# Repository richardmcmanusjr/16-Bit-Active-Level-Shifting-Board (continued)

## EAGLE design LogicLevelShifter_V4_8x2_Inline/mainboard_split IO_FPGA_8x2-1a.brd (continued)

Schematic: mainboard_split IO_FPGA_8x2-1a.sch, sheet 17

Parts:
C94, C95: 0.1uF; C0805
C96, C97: 2.2uF; C0805
FROM_FPGA_20: PINHD-1X1; 1X01
JP_DRAIN19: PINHD-1X1; 1X01
JP_GATE20: PINHD-1X1; 1X01
JP_MIPS20: PINHD-1X1; 1X01
R186, R190, R192: 130; R0805
R187: 130; R0603
R188, R189, R191, R193, R194: 220; R0805
S39, S40: SM-3TW102; SM3TW102
TO_FPGA_20: PINHD-1X1; 1X01
U44, U45: TLV3501AID; D8

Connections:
+1.5V: C94.2, C96.2, S39.1 (CCW), S40.1 (CCW), U44.7 (V+); also elsewhere on the board
+3V: C95.1, C97.1, U45.7 (V+); also elsewhere on the board
-1.5V: C94.1, C96.1, S39.3 (CW), U44.4 (V-); also elsewhere on the board
DIR_GATE: JP_GATE20.1, R194.2; also elsewhere on the board
F16: FROM_FPGA_20.1, R187.1; also elsewhere on the board
GND: C95.2, C97.2, R189.2, R193.2, S40.3 (CW), U45.4 (V-); also elsewhere on the board
INV_DIR_DRAIN: JP_DRAIN19.1, U45.8 (SHDN); also elsewhere on the board
M16: JP_MIPS20.1, R191.2, R192.1, R193.1; also elsewhere on the board
unnamed: R186.2, S39.2 (WIPER)
unnamed: R186.1, U44.2 (IN-)
unnamed: R188.1, U45.6 (OUT)
unnamed: R190.1, S40.2 (WIPER)
unnamed: R190.2, U45.2 (IN-)
unnamed: R192.2, U45.3 (IN+)
unnamed: R191.1, U44.6 (OUT)
unnamed: R194.1, U44.8 (SHDN)
unnamed: R187.2, U44.3 (IN+)
TF16: R188.2, R189.1, TO_FPGA_20.1; also elsewhere on the board

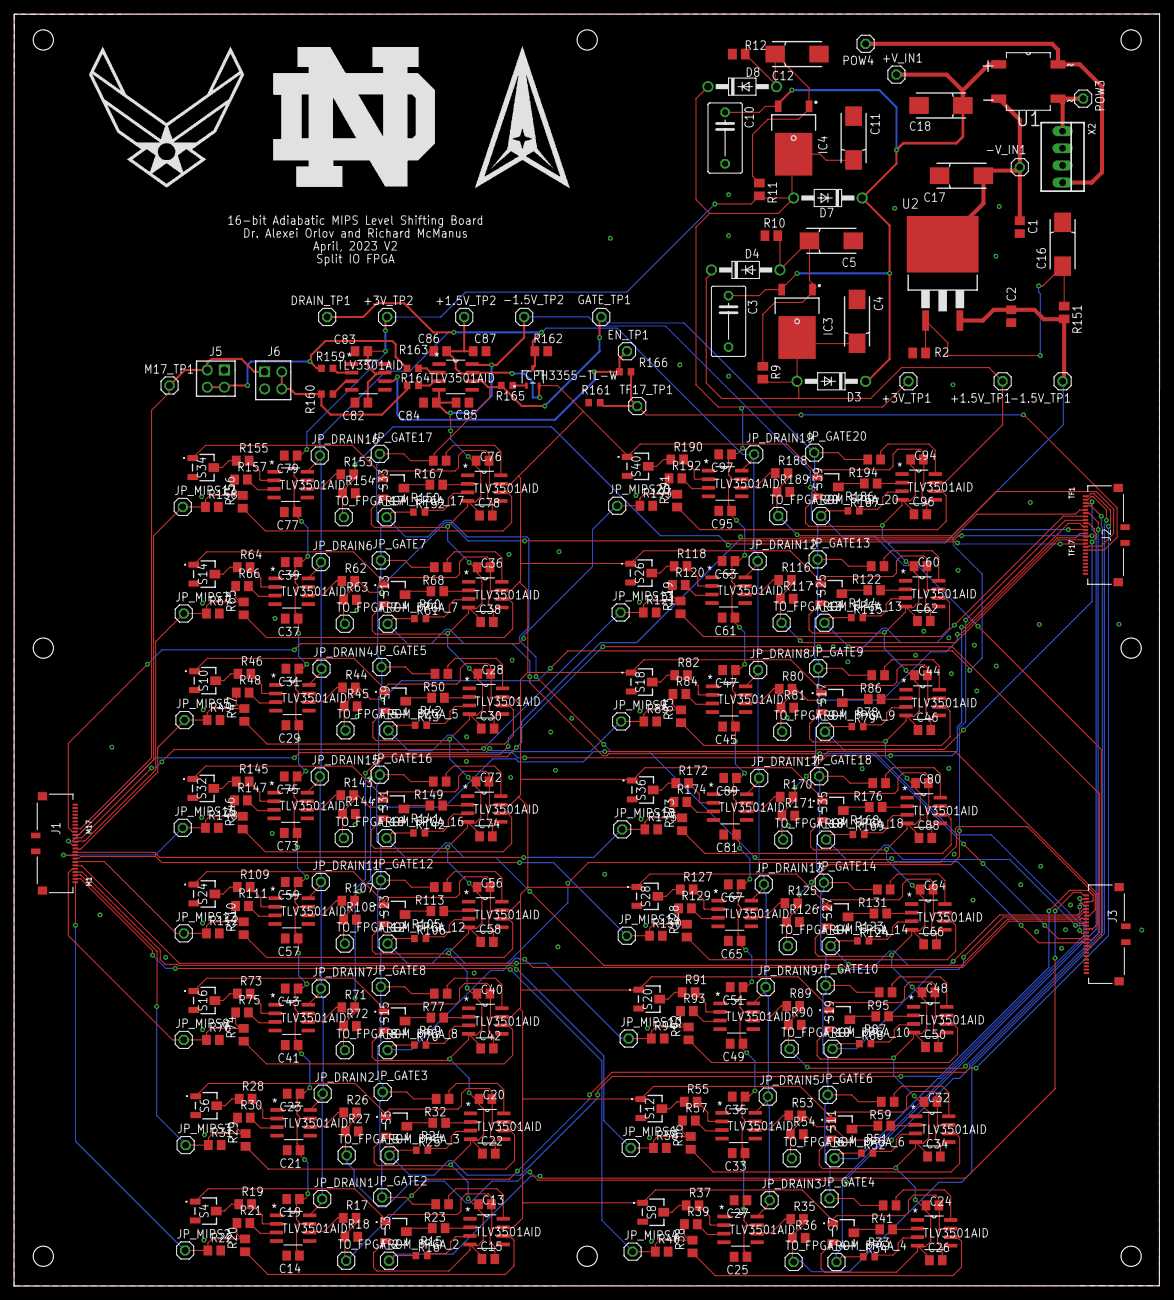
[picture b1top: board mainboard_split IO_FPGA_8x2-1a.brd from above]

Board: 2 copper layers, 169.8 x 188.6 mm, 415 parts (0 on the bottom side), 215 nets.

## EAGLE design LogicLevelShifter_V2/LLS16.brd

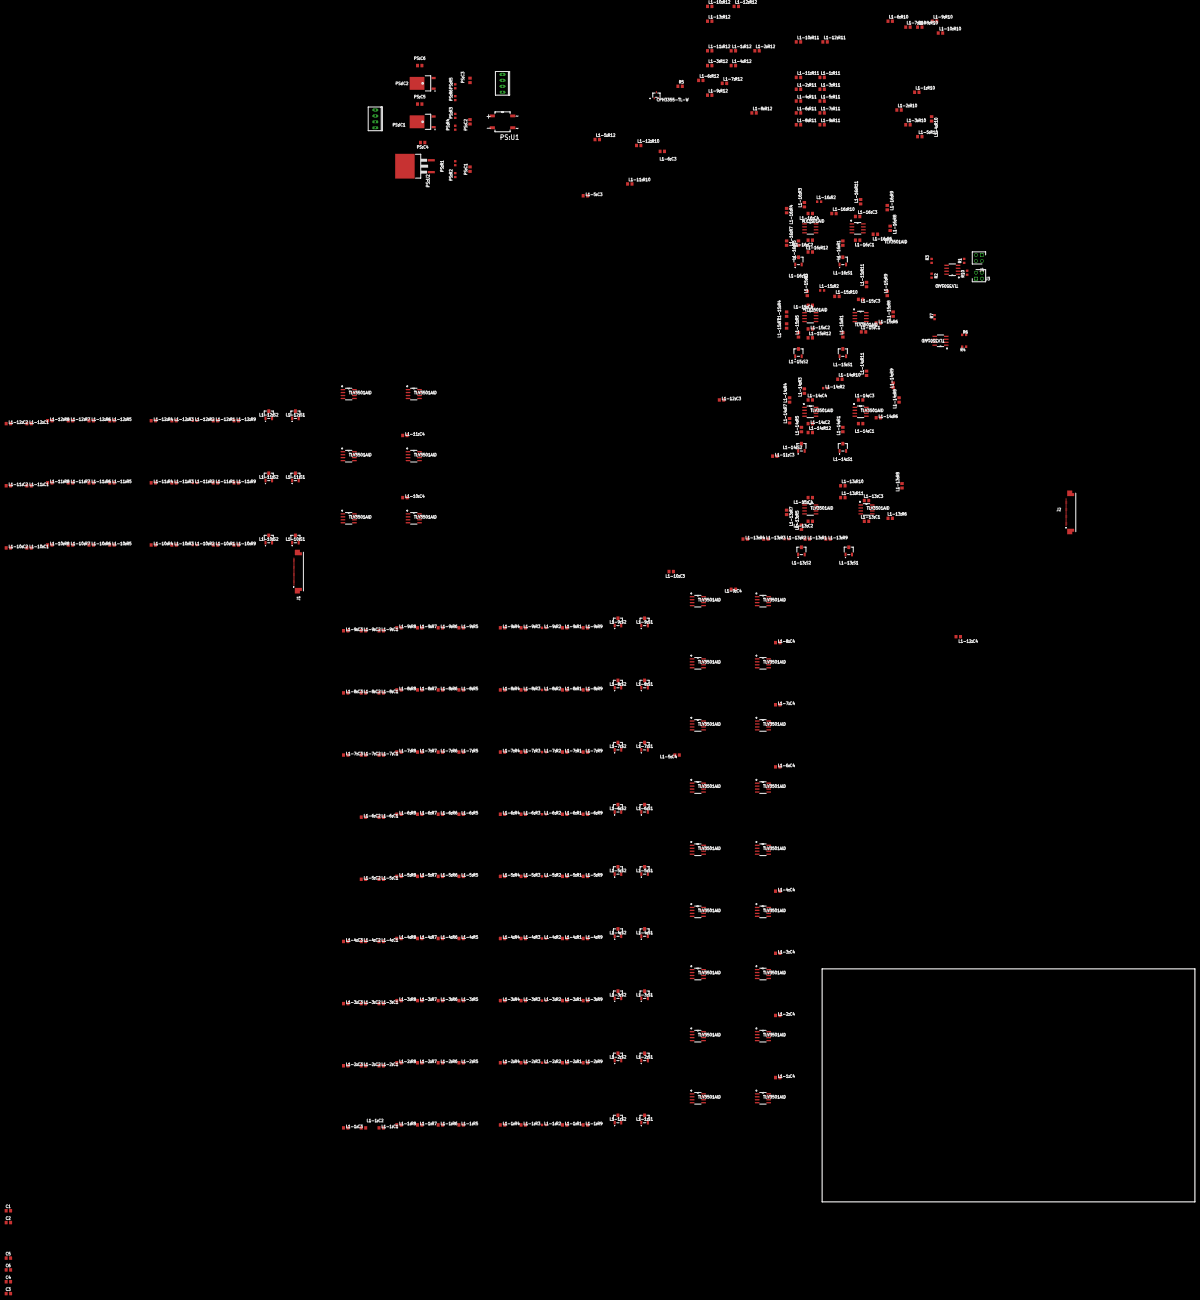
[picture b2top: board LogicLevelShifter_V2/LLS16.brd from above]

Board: 2 copper layers, 160.0 x 100.0 mm, 359 parts (0 on the bottom side), 264 nets, no tracks yet.

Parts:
C1, C2, C3, C4, C5, C6: C0805
J1, J2: 0524372471
J3, J4: 70287-1098; HDRV4W64P254_2X2_521X508X851P
L1-1:C1, L1-1:C2, L1-1:C3, L1-1:C4, L1-2:C1, L1-2:C2, L1-2:C3, L1-2:C4, L1-3:C1, L1-3:C2, L1-3:C3, L1-3:C4, L1-4:C1, L1-4:C2, L1-4:C3, L1-4:C4, L1-5:C1, L1-5:C2, L1-5:C3, L1-5:C4, L1-6:C1, L1-6:C2, L1-6:C3, L1-6:C4, L1-7:C1, L1-7:C2, L1-7:C3, L1-7:C4, L1-8:C1, L1-8:C2, L1-8:C3, L1-8:C4, L1-9:C1, L1-9:C2, L1-9:C3, L1-9:C4, L1-10:C1, L1-10:C2, L1-10:C3, L1-10:C4, L1-11:C1, L1-11:C2, L1-11:C3, L1-11:C4, L1-12:C1, L1-12:C2, L1-12:C3, L1-12:C4, L1-13:C1, L1-13:C2, L1-13:C3, L1-13:C4, L1-14:C1, L1-14:C2, L1-14:C3, L1-14:C4, L1-15:C1, L1-15:C2, L1-15:C3, L1-15:C4, L1-16:C1, L1-16:C2, L1-16:C3, L1-16:C4: C0805
L1-1:R1, L1-1:R5, L1-1:R7, L1-2:R1, L1-2:R5, L1-2:R7, L1-3:R1, L1-3:R5, L1-3:R7, L1-4:R1, L1-4:R5, L1-4:R7, L1-5:R1, L1-5:R5, L1-5:R7, L1-6:R1, L1-6:R5, L1-6:R7, L1-7:R1, L1-7:R5, L1-7:R7, L1-8:R1, L1-8:R5, L1-8:R7, L1-9:R1, L1-9:R5, L1-9:R7, L1-10:R1, L1-10:R5, L1-10:R7, L1-11:R1, L1-11:R5, L1-11:R7, L1-12:R1, L1-12:R5, L1-12:R7, L1-13:R1, L1-13:R5, L1-13:R7, L1-14:R1, L1-14:R5, L1-14:R7, L1-15:R1, L1-15:R5, L1-15:R7, L1-16:R1, L1-16:R5, L1-16:R7: 130; R0805
L1-1:R2, L1-2:R2, L1-3:R2, L1-4:R2, L1-5:R2, L1-6:R2, L1-7:R2, L1-8:R2, L1-9:R2, L1-10:R2, L1-11:R2, L1-12:R2, L1-13:R2, L1-14:R2, L1-15:R2, L1-16:R2: 130; R0603
L1-1:R3, L1-1:R4, L1-1:R6, L1-1:R8, L1-1:R9, L1-2:R3, L1-2:R4, L1-2:R6, L1-2:R8, L1-2:R9, L1-3:R3, L1-3:R4, L1-3:R6, L1-3:R8, L1-3:R9, L1-4:R3, L1-4:R4, L1-4:R6, L1-4:R8, L1-4:R9, L1-5:R3, L1-5:R4, L1-5:R6, L1-5:R8, L1-5:R9, L1-6:R3, L1-6:R4, L1-6:R6, L1-6:R8, L1-6:R9, L1-7:R3, L1-7:R4, L1-7:R6, L1-7:R8, L1-7:R9, L1-8:R3, L1-8:R4, L1-8:R6, L1-8:R8, L1-8:R9, L1-9:R3, L1-9:R4, L1-9:R6, L1-9:R8, L1-9:R9, L1-10:R3, L1-10:R4, L1-10:R6, L1-10:R8, L1-10:R9, L1-11:R3, L1-11:R4, L1-11:R6, L1-11:R8, L1-11:R9, L1-12:R3, L1-12:R4, L1-12:R6, L1-12:R8, L1-12:R9, L1-13:R3, L1-13:R4, L1-13:R6, L1-13:R8, L1-13:R9, L1-14:R3, L1-14:R4, L1-14:R6, L1-14:R8, L1-14:R9, L1-15:R3, L1-15:R4, L1-15:R6, L1-15:R8, L1-15:R9, L1-16:R3, L1-16:R4, L1-16:R6, L1-16:R8, L1-16:R9: 220; R0805
L1-1:R10, L1-1:R11, L1-1:R12, L1-2:R10, L1-2:R11, L1-2:R12, L1-3:R10, L1-3:R11, L1-3:R12, L1-4:R10, L1-4:R11, L1-4:R12, L1-5:R10, L1-5:R11, L1-5:R12, L1-6:R10, L1-6:R11, L1-6:R12, L1-7:R10, L1-7:R11, L1-7:R12, L1-8:R10, L1-8:R11, L1-8:R12, L1-9:R10, L1-9:R11, L1-9:R12, L1-10:R10, L1-10:R11, L1-10:R12, L1-11:R10, L1-11:R11, L1-11:R12, L1-12:R10, L1-12:R11, L1-12:R12, L1-13:R10, L1-13:R11, L1-13:R12, L1-14:R10, L1-14:R11, L1-14:R12, L1-15:R10, L1-15:R11, L1-15:R12, L1-16:R10, L1-16:R11, L1-16:R12: 0; R0805
L1-1:S1, L1-1:S2, L1-2:S1, L1-2:S2, L1-3:S1, L1-3:S2, L1-4:S1, L1-4:S2, L1-5:S1, L1-5:S2, L1-6:S1, L1-6:S2, L1-7:S1, L1-7:S2, L1-8:S1, L1-8:S2, L1-9:S1, L1-9:S2, L1-10:S1, L1-10:S2, L1-11:S1, L1-11:S2, L1-12:S1, L1-12:S2, L1-13:S1, L1-13:S2, L1-14:S1, L1-14:S2, L1-15:S1, L1-15:S2, L1-16:S1, L1-16:S2: SM-3TW102; SM3TW102
L1-1:U1, L1-1:U2, L1-2:U1, L1-2:U2, L1-3:U1, L1-3:U2, L1-4:U1, L1-4:U2, L1-5:U1, L1-5:U2, L1-6:U1, L1-6:U2, L1-7:U1, L1-7:U2, L1-8:U1, L1-8:U2, L1-9:U1, L1-9:U2, L1-10:U1, L1-10:U2, L1-11:U1, L1-11:U2, L1-12:U1, L1-12:U2, L1-13:U1, L1-13:U2, L1-14:U1, L1-14:U2, L1-15:U1, L1-15:U2, L1-16:U1, L1-16:U2: TLV3501AID; D8
PS:C1, PS:C2, PS:C3: 10uF; C0805
PS:C4, PS:C5, PS:C6: 0.1uF; C0805
PS:IC1, PS:IC2: LM317AMDT_NOPB; TO228P991X238-3N
PS:R1, PS:R3, PS:R5: 240; R0603
PS:R2, PS:R4, PS:R6: 49.9; R0603
PS:U1: DF10S; SOT508P985X260-4N
PS:U2: MC79GENERICD2T; D2PAK-3
R1, R2, R3, R4, R6, R7, R10: 220; R0603
R5: 51; R0805
U1: CPH3355-TL-W; CPH3_2P9X1P6_ONS
U2, U3: TLV3501AID; D8
U$1, U$2: CONNHEADERVERT4POS2.54MM

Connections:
+1.5V: C3.2, C4.2, L1-1:R11.2, L1-1:S1.3, L1-1:S2.1, L1-2:R11.2, L1-2:S1.3, L1-2:S2.1, L1-3:R11.2, L1-3:S1.3, L1-3:S2.1, L1-4:R11.2, L1-4:S1.3, L1-4:S2.1, L1-5:R11.2, L1-5:S1.3, L1-5:S2.1, L1-6:R11.2, L1-6:S1.3, L1-6:S2.1, L1-7:R11.2, L1-7:S1.3, L1-7:S2.1, L1-8:R11.2, L1-8:S1.3, L1-8:S2.1, L1-9:R11.2, L1-9:S1.3, L1-9:S2.1, L1-10:R11.2, L1-10:S1.3, L1-10:S2.1, L1-11:R11.2, L1-11:S1.3, L1-11:S2.1, L1-12:R11.2, L1-12:S1.3, L1-12:S2.1, L1-13:R11.2, L1-13:S1.3, L1-13:S2.1, L1-14:R11.2, L1-14:S1.3, L1-14:S2.1, L1-15:R11.2, L1-15:S1.3, L1-15:S2.1, L1-16:R11.2, L1-16:S1.3, L1-16:S2.1, PS:C5.1, PS:IC1.4, PS:R3.2, U1.2, U3.7, U$2.3
+3V: C1.2, C2.2, L1-1:R12.1, L1-2:R12.1, L1-3:R12.1, L1-4:R12.1, L1-5:R12.1, L1-6:R12.1, L1-7:R12.1, L1-8:R12.1, L1-9:R12.1, L1-10:R12.1, L1-11:R12.1, L1-12:R12.1, L1-13:R12.1, L1-14:R12.1, L1-15:R12.1, L1-16:R12.1, PS:C6.1, PS:IC2.4, PS:R5.2, U2.7, U$2.4
+5V: PS:U1.4, U$1.4
-1.5V: C5.1, C6.1, L1-1:R10.1, L1-1:S1.1, L1-2:R10.1, L1-2:S1.1, L1-3:R10.1, L1-3:S1.1, L1-4:R10.1, L1-4:S1.1, L1-5:R10.1, L1-5:S1.1, L1-6:R10.1, L1-6:S1.1, L1-7:R10.1, L1-7:S1.1, L1-8:R10.1, L1-8:S1.1, L1-9:R10.1, L1-9:S1.1, L1-10:R10.1, L1-10:S1.1, L1-11:R10.1, L1-11:S1.1, L1-12:R10.1, L1-12:S1.1, L1-13:R10.1, L1-13:S1.1, L1-14:R10.1, L1-14:S1.1, L1-15:R10.1, L1-15:S1.1, L1-16:R10.1, L1-16:S1.1, U3.4, U3.8, U$2.1
D: L1-1:U2.8, L1-2:U2.8, L1-3:U2.8, L1-4:U2.8, L1-5:U2.8, L1-6:U2.8, L1-7:U2.8, L1-8:U2.8, L1-9:U2.8, L1-10:U2.8, L1-11:U2.8, L1-12:U2.8, L1-13:U2.8, L1-14:U2.8, L1-15:U2.8, L1-16:U2.8, R5.1, U1.3
F1: J1.1, L1-1:R2.1, L1-1:R3.2, L1-1:R4.1
F2: J1.2, L1-2:R2.1, L1-2:R3.2, L1-2:R4.1
F3: J1.3, L1-3:R2.1, L1-3:R3.2, L1-3:R4.1
F4: J1.4, L1-4:R2.1, L1-4:R3.2, L1-4:R4.1
F5: J1.5, L1-5:R2.1, L1-5:R3.2, L1-5:R4.1
F6: J1.6, L1-6:R2.1, L1-6:R3.2, L1-6:R4.1
F7: J1.7, L1-7:R2.1, L1-7:R3.2, L1-7:R4.1
F8: J1.8, L1-8:R2.1, L1-8:R3.2, L1-8:R4.1
F9: J1.9, L1-9:R2.1, L1-9:R3.2, L1-9:R4.1
F10: J1.10, L1-10:R2.1, L1-10:R3.2, L1-10:R4.1
F11: J1.11, L1-11:R2.1, L1-11:R3.2, L1-11:R4.1
F12: J1.12, L1-12:R2.1, L1-12:R3.2, L1-12:R4.1
F13: J1.13, L1-13:R2.1, L1-13:R3.2, L1-13:R4.1
F14: J1.14, L1-14:R2.1, L1-14:R3.2, L1-14:R4.1
F15: J1.15, L1-15:R2.1, L1-15:R3.2, L1-15:R4.1
F16: J1.16, L1-16:R2.1, L1-16:R3.2, L1-16:R4.1
F17: J1.17, R2.2, R3.2
G: L1-1:R9.2, L1-2:R9.2, L1-3:R9.2, L1-4:R9.2, L1-5:R9.2, L1-6:R9.2, L1-7:R9.2, L1-8:R9.2, L1-9:R9.2, L1-10:R9.2, L1-11:R9.2, L1-12:R9.2, L1-13:R9.2, L1-14:R9.2, L1-15:R9.2, L1-16:R9.2, R7.1, U3.6
GND: C1.1, C2.1, C3.1, C4.1, C5.2, C6.2, J3.1, J4.3, PS:C1.2, PS:C2.2, PS:C3.2, PS:C4.2, PS:C5.2, PS:C6.2, PS:R2.1, PS:R4.1, PS:R6.1, R2.1, R5.2, U2.4, U2.8, U$1.2, U$1.3, U$2.2
L1-1:GND!: L1-1:C2.2, L1-1:C4.2, L1-1:R4.2, L1-1:R8.2, L1-1:S2.3, L1-1:U2.4
L1-1:N$1: L1-1:R1.2, L1-1:S1.2
L1-1:N$2: L1-1:R1.1, L1-1:U1.2
L1-1:N$3: L1-1:R2.2, L1-1:U1.3
L1-1:N$4: L1-1:C1.1, L1-1:C3.1, L1-1:R10.2, L1-1:U1.4
L1-1:N$5: L1-1:R3.1, L1-1:U2.6
L1-1:N$6: L1-1:R5.1, L1-1:S2.2
L1-1:N$7: L1-1:R5.2, L1-1:U2.2
L1-1:N$8: L1-1:R7.2, L1-1:U2.3
L1-1:N$9: L1-1:C1.2, L1-1:C3.2, L1-1:R11.1, L1-1:U1.7
L1-1:N$10: L1-1:R6.1, L1-1:U1.6
L1-1:N$11: L1-1:R9.1, L1-1:U1.8
L1-1:N$12: L1-1:C2.1, L1-1:C4.1, L1-1:R12.2, L1-1:U2.7
L1-2:GND!: L1-2:C2.2, L1-2:C4.2, L1-2:R4.2, L1-2:R8.2, L1-2:S2.3, L1-2:U2.4
L1-2:N$1: L1-2:R1.2, L1-2:S1.2
L1-2:N$2: L1-2:R1.1, L1-2:U1.2
L1-2:N$3: L1-2:R2.2, L1-2:U1.3
L1-2:N$4: L1-2:C1.1, L1-2:C3.1, L1-2:R10.2, L1-2:U1.4
L1-2:N$5: L1-2:R3.1, L1-2:U2.6
L1-2:N$6: L1-2:R5.1, L1-2:S2.2
L1-2:N$7: L1-2:R5.2, L1-2:U2.2
L1-2:N$8: L1-2:R7.2, L1-2:U2.3
L1-2:N$9: L1-2:C1.2, L1-2:C3.2, L1-2:R11.1, L1-2:U1.7
L1-2:N$10: L1-2:R6.1, L1-2:U1.6
L1-2:N$11: L1-2:R9.1, L1-2:U1.8
L1-2:N$12: L1-2:C2.1, L1-2:C4.1, L1-2:R12.2, L1-2:U2.7
L1-3:GND!: L1-3:C2.2, L1-3:C4.2, L1-3:R4.2, L1-3:R8.2, L1-3:S2.3, L1-3:U2.4
L1-3:N$1: L1-3:R1.2, L1-3:S1.2
L1-3:N$2: L1-3:R1.1, L1-3:U1.2
L1-3:N$3: L1-3:R2.2, L1-3:U1.3
L1-3:N$4: L1-3:C1.1, L1-3:C3.1, L1-3:R10.2, L1-3:U1.4
L1-3:N$5: L1-3:R3.1, L1-3:U2.6
L1-3:N$6: L1-3:R5.1, L1-3:S2.2
L1-3:N$7: L1-3:R5.2, L1-3:U2.2
L1-3:N$8: L1-3:R7.2, L1-3:U2.3
L1-3:N$9: L1-3:C1.2, L1-3:C3.2, L1-3:R11.1, L1-3:U1.7
L1-3:N$10: L1-3:R6.1, L1-3:U1.6
L1-3:N$11: L1-3:R9.1, L1-3:U1.8
L1-3:N$12: L1-3:C2.1, L1-3:C4.1, L1-3:R12.2, L1-3:U2.7
L1-4:GND!: L1-4:C2.2, L1-4:C4.2, L1-4:R4.2, L1-4:R8.2, L1-4:S2.3, L1-4:U2.4
L1-4:N$1: L1-4:R1.2, L1-4:S1.2
L1-4:N$2: L1-4:R1.1, L1-4:U1.2
L1-4:N$3: L1-4:R2.2, L1-4:U1.3
L1-4:N$4: L1-4:C1.1, L1-4:C3.1, L1-4:R10.2, L1-4:U1.4
L1-4:N$5: L1-4:R3.1, L1-4:U2.6
L1-4:N$6: L1-4:R5.1, L1-4:S2.2
L1-4:N$7: L1-4:R5.2, L1-4:U2.2
L1-4:N$8: L1-4:R7.2, L1-4:U2.3
L1-4:N$9: L1-4:C1.2, L1-4:C3.2, L1-4:R11.1, L1-4:U1.7
L1-4:N$10: L1-4:R6.1, L1-4:U1.6
L1-4:N$11: L1-4:R9.1, L1-4:U1.8
L1-4:N$12: L1-4:C2.1, L1-4:C4.1, L1-4:R12.2, L1-4:U2.7
L1-5:GND!: L1-5:C2.2, L1-5:C4.2, L1-5:R4.2, L1-5:R8.2, L1-5:S2.3, L1-5:U2.4
L1-5:N$1: L1-5:R1.2, L1-5:S1.2
L1-5:N$2: L1-5:R1.1, L1-5:U1.2
L1-5:N$3: L1-5:R2.2, L1-5:U1.3
L1-5:N$4: L1-5:C1.1, L1-5:C3.1, L1-5:R10.2, L1-5:U1.4
L1-5:N$5: L1-5:R3.1, L1-5:U2.6
L1-5:N$6: L1-5:R5.1, L1-5:S2.2
L1-5:N$7: L1-5:R5.2, L1-5:U2.2
L1-5:N$8: L1-5:R7.2, L1-5:U2.3
L1-5:N$9: L1-5:C1.2, L1-5:C3.2, L1-5:R11.1, L1-5:U1.7
L1-5:N$10: L1-5:R6.1, L1-5:U1.6
L1-5:N$11: L1-5:R9.1, L1-5:U1.8
L1-5:N$12: L1-5:C2.1, L1-5:C4.1, L1-5:R12.2, L1-5:U2.7
L1-6:GND!: L1-6:C2.2, L1-6:C4.2, L1-6:R4.2, L1-6:R8.2, L1-6:S2.3, L1-6:U2.4
L1-6:N$1: L1-6:R1.2, L1-6:S1.2
L1-6:N$2: L1-6:R1.1, L1-6:U1.2
L1-6:N$3: L1-6:R2.2, L1-6:U1.3
L1-6:N$4: L1-6:C1.1, L1-6:C3.1, L1-6:R10.2, L1-6:U1.4
L1-6:N$5: L1-6:R3.1, L1-6:U2.6
L1-6:N$6: L1-6:R5.1, L1-6:S2.2
L1-6:N$7: L1-6:R5.2, L1-6:U2.2
L1-6:N$8: L1-6:R7.2, L1-6:U2.3
L1-6:N$9: L1-6:C1.2, L1-6:C3.2, L1-6:R11.1, L1-6:U1.7
L1-6:N$10: L1-6:R6.1, L1-6:U1.6
L1-6:N$11: L1-6:R9.1, L1-6:U1.8
L1-6:N$12: L1-6:C2.1, L1-6:C4.1, L1-6:R12.2, L1-6:U2.7
L1-7:GND!: L1-7:C2.2, L1-7:C4.2, L1-7:R4.2, L1-7:R8.2, L1-7:S2.3, L1-7:U2.4
L1-7:N$1: L1-7:R1.2, L1-7:S1.2
L1-7:N$2: L1-7:R1.1, L1-7:U1.2
L1-7:N$3: L1-7:R2.2, L1-7:U1.3
L1-7:N$4: L1-7:C1.1, L1-7:C3.1, L1-7:R10.2, L1-7:U1.4
L1-7:N$5: L1-7:R3.1, L1-7:U2.6
L1-7:N$6: L1-7:R5.1, L1-7:S2.2
L1-7:N$7: L1-7:R5.2, L1-7:U2.2
L1-7:N$8: L1-7:R7.2, L1-7:U2.3
L1-7:N$9: L1-7:C1.2, L1-7:C3.2, L1-7:R11.1, L1-7:U1.7
L1-7:N$10: L1-7:R6.1, L1-7:U1.6
L1-7:N$11: L1-7:R9.1, L1-7:U1.8
L1-7:N$12: L1-7:C2.1, L1-7:C4.1, L1-7:R12.2, L1-7:U2.7
L1-8:GND!: L1-8:C2.2, L1-8:C4.2, L1-8:R4.2, L1-8:R8.2, L1-8:S2.3, L1-8:U2.4
L1-8:N$1: L1-8:R1.2, L1-8:S1.2
L1-8:N$2: L1-8:R1.1, L1-8:U1.2
L1-8:N$3: L1-8:R2.2, L1-8:U1.3
L1-8:N$4: L1-8:C1.1, L1-8:C3.1, L1-8:R10.2, L1-8:U1.4
L1-8:N$5: L1-8:R3.1, L1-8:U2.6
L1-8:N$6: L1-8:R5.1, L1-8:S2.2
L1-8:N$7: L1-8:R5.2, L1-8:U2.2
L1-8:N$8: L1-8:R7.2, L1-8:U2.3
L1-8:N$9: L1-8:C1.2, L1-8:C3.2, L1-8:R11.1, L1-8:U1.7
L1-8:N$10: L1-8:R6.1, L1-8:U1.6
L1-8:N$11: L1-8:R9.1, L1-8:U1.8
L1-8:N$12: L1-8:C2.1, L1-8:C4.1, L1-8:R12.2, L1-8:U2.7
L1-9:GND!: L1-9:C2.2, L1-9:C4.2, L1-9:R4.2, L1-9:R8.2, L1-9:S2.3, L1-9:U2.4
L1-9:N$1: L1-9:R1.2, L1-9:S1.2
L1-9:N$2: L1-9:R1.1, L1-9:U1.2
L1-9:N$3: L1-9:R2.2, L1-9:U1.3
L1-9:N$4: L1-9:C1.1, L1-9:C3.1, L1-9:R10.2, L1-9:U1.4
L1-9:N$5: L1-9:R3.1, L1-9:U2.6
L1-9:N$6: L1-9:R5.1, L1-9:S2.2
L1-9:N$7: L1-9:R5.2, L1-9:U2.2
L1-9:N$8: L1-9:R7.2, L1-9:U2.3
L1-9:N$9: L1-9:C1.2, L1-9:C3.2, L1-9:R11.1, L1-9:U1.7
L1-9:N$10: L1-9:R6.1, L1-9:U1.6
L1-9:N$11: L1-9:R9.1, L1-9:U1.8
L1-9:N$12: L1-9:C2.1, L1-9:C4.1, L1-9:R12.2, L1-9:U2.7
L1-10:GND!: L1-10:C2.2, L1-10:C4.2, L1-10:R4.2, L1-10:R8.2, L1-10:S2.3, L1-10:U2.4
L1-10:N$1: L1-10:R1.2, L1-10:S1.2
L1-10:N$2: L1-10:R1.1, L1-10:U1.2
L1-10:N$3: L1-10:R2.2, L1-10:U1.3
L1-10:N$4: L1-10:C1.1, L1-10:C3.1, L1-10:R10.2, L1-10:U1.4
L1-10:N$5: L1-10:R3.1, L1-10:U2.6
L1-10:N$6: L1-10:R5.1, L1-10:S2.2
L1-10:N$7: L1-10:R5.2, L1-10:U2.2
L1-10:N$8: L1-10:R7.2, L1-10:U2.3
L1-10:N$9: L1-10:C1.2, L1-10:C3.2, L1-10:R11.1, L1-10:U1.7
L1-10:N$10: L1-10:R6.1, L1-10:U1.6
L1-10:N$11: L1-10:R9.1, L1-10:U1.8
L1-10:N$12: L1-10:C2.1, L1-10:C4.1, L1-10:R12.2, L1-10:U2.7
L1-11:GND!: L1-11:C2.2, L1-11:C4.2, L1-11:R4.2, L1-11:R8.2, L1-11:S2.3, L1-11:U2.4
L1-11:N$1: L1-11:R1.2, L1-11:S1.2
L1-11:N$2: L1-11:R1.1, L1-11:U1.2
L1-11:N$3: L1-11:R2.2, L1-11:U1.3
L1-11:N$4: L1-11:C1.1, L1-11:C3.1, L1-11:R10.2, L1-11:U1.4
L1-11:N$5: L1-11:R3.1, L1-11:U2.6
L1-11:N$6: L1-11:R5.1, L1-11:S2.2
L1-11:N$7: L1-11:R5.2, L1-11:U2.2
L1-11:N$8: L1-11:R7.2, L1-11:U2.3
L1-11:N$9: L1-11:C1.2, L1-11:C3.2, L1-11:R11.1, L1-11:U1.7
L1-11:N$10: L1-11:R6.1, L1-11:U1.6
L1-11:N$11: L1-11:R9.1, L1-11:U1.8
L1-11:N$12: L1-11:C2.1, L1-11:C4.1, L1-11:R12.2, L1-11:U2.7
L1-12:GND!: L1-12:C2.2, L1-12:C4.2, L1-12:R4.2, L1-12:R8.2, L1-12:S2.3, L1-12:U2.4
L1-12:N$1: L1-12:R1.2, L1-12:S1.2
L1-12:N$2: L1-12:R1.1, L1-12:U1.2
L1-12:N$3: L1-12:R2.2, L1-12:U1.3
L1-12:N$4: L1-12:C1.1, L1-12:C3.1, L1-12:R10.2, L1-12:U1.4
L1-12:N$5: L1-12:R3.1, L1-12:U2.6
L1-12:N$6: L1-12:R5.1, L1-12:S2.2
L1-12:N$7: L1-12:R5.2, L1-12:U2.2
L1-12:N$8: L1-12:R7.2, L1-12:U2.3
L1-12:N$9: L1-12:C1.2, L1-12:C3.2, L1-12:R11.1, L1-12:U1.7
L1-12:N$10: L1-12:R6.1, L1-12:U1.6
L1-12:N$11: L1-12:R9.1, L1-12:U1.8
L1-12:N$12: L1-12:C2.1, L1-12:C4.1, L1-12:R12.2, L1-12:U2.7
L1-13:GND!: L1-13:C2.2, L1-13:C4.2, L1-13:R4.2, L1-13:R8.2, L1-13:S2.3, L1-13:U2.4
L1-13:N$1: L1-13:R1.2, L1-13:S1.2
L1-13:N$2: L1-13:R1.1, L1-13:U1.2
L1-13:N$3: L1-13:R2.2, L1-13:U1.3
L1-13:N$4: L1-13:C1.1, L1-13:C3.1, L1-13:R10.2, L1-13:U1.4
L1-13:N$5: L1-13:R3.1, L1-13:U2.6
L1-13:N$6: L1-13:R5.1, L1-13:S2.2
L1-13:N$7: L1-13:R5.2, L1-13:U2.2
L1-13:N$8: L1-13:R7.2, L1-13:U2.3
L1-13:N$9: L1-13:C1.2, L1-13:C3.2, L1-13:R11.1, L1-13:U1.7
L1-13:N$10: L1-13:R6.1, L1-13:U1.6
L1-13:N$11: L1-13:R9.1, L1-13:U1.8
L1-13:N$12: L1-13:C2.1, L1-13:C4.1, L1-13:R12.2, L1-13:U2.7
L1-14:GND!: L1-14:C2.2, L1-14:C4.2, L1-14:R4.2, L1-14:R8.2, L1-14:S2.3, L1-14:U2.4
L1-14:N$1: L1-14:R1.2, L1-14:S1.2
L1-14:N$2: L1-14:R1.1, L1-14:U1.2
L1-14:N$3: L1-14:R2.2, L1-14:U1.3
L1-14:N$4: L1-14:C1.1, L1-14:C3.1, L1-14:R10.2, L1-14:U1.4
L1-14:N$5: L1-14:R3.1, L1-14:U2.6
L1-14:N$6: L1-14:R5.1, L1-14:S2.2
L1-14:N$7: L1-14:R5.2, L1-14:U2.2
L1-14:N$8: L1-14:R7.2, L1-14:U2.3
L1-14:N$9: L1-14:C1.2, L1-14:C3.2, L1-14:R11.1, L1-14:U1.7
L1-14:N$10: L1-14:R6.1, L1-14:U1.6
L1-14:N$11: L1-14:R9.1, L1-14:U1.8
L1-14:N$12: L1-14:C2.1, L1-14:C4.1, L1-14:R12.2, L1-14:U2.7
L1-15:GND!: L1-15:C2.2, L1-15:C4.2, L1-15:R4.2, L1-15:R8.2, L1-15:S2.3, L1-15:U2.4
L1-15:N$1: L1-15:R1.2, L1-15:S1.2
L1-15:N$2: L1-15:R1.1, L1-15:U1.2
L1-15:N$3: L1-15:R2.2, L1-15:U1.3
L1-15:N$4: L1-15:C1.1, L1-15:C3.1, L1-15:R10.2, L1-15:U1.4
L1-15:N$5: L1-15:R3.1, L1-15:U2.6
L1-15:N$6: L1-15:R5.1, L1-15:S2.2
L1-15:N$7: L1-15:R5.2, L1-15:U2.2
L1-15:N$8: L1-15:R7.2, L1-15:U2.3
L1-15:N$9: L1-15:C1.2, L1-15:C3.2, L1-15:R11.1, L1-15:U1.7
L1-15:N$10: L1-15:R6.1, L1-15:U1.6
L1-15:N$11: L1-15:R9.1, L1-15:U1.8
L1-15:N$12: L1-15:C2.1, L1-15:C4.1, L1-15:R12.2, L1-15:U2.7
L1-16:GND!: L1-16:C2.2, L1-16:C4.2, L1-16:R4.2, L1-16:R8.2, L1-16:S2.3, L1-16:U2.4
L1-16:N$1: L1-16:R1.2, L1-16:S1.2
L1-16:N$2: L1-16:R1.1, L1-16:U1.2
L1-16:N$3: L1-16:R2.2, L1-16:U1.3
L1-16:N$4: L1-16:C1.1, L1-16:C3.1, L1-16:R10.2, L1-16:U1.4
L1-16:N$5: L1-16:R3.1, L1-16:U2.6
L1-16:N$6: L1-16:R5.1, L1-16:S2.2
L1-16:N$7: L1-16:R5.2, L1-16:U2.2
L1-16:N$8: L1-16:R7.2, L1-16:U2.3
L1-16:N$9: L1-16:C1.2, L1-16:C3.2, L1-16:R11.1, L1-16:U1.7
L1-16:N$10: L1-16:R6.1, L1-16:U1.6
L1-16:N$11: L1-16:R9.1, L1-16:U1.8
L1-16:N$12: L1-16:C2.1, L1-16:C4.1, L1-16:R12.2, L1-16:U2.7
M1: J2.1, L1-1:R6.2, L1-1:R7.1, L1-1:R8.1
M2: J2.2, L1-2:R6.2, L1-2:R7.1, L1-2:R8.1
M3: J2.3, L1-3:R6.2, L1-3:R7.1, L1-3:R8.1
M4: J2.4, L1-4:R6.2, L1-4:R7.1, L1-4:R8.1
M5: J2.5, L1-5:R6.2, L1-5:R7.1, L1-5:R8.1
M6: J2.6, L1-6:R6.2, L1-6:R7.1, L1-6:R8.1
M7: J2.7, L1-7:R6.2, L1-7:R7.1, L1-7:R8.1
M8: J2.8, L1-8:R6.2, L1-8:R7.1, L1-8:R8.1
M9: J2.9, L1-9:R6.2, L1-9:R7.1, L1-9:R8.1
M10: J2.10, L1-10:R6.2, L1-10:R7.1, L1-10:R8.1
M11: J2.11, L1-11:R6.2, L1-11:R7.1, L1-11:R8.1
M12: J2.12, L1-12:R6.2, L1-12:R7.1, L1-12:R8.1
M13: J2.13, L1-13:R6.2, L1-13:R7.1, L1-13:R8.1
M14: J2.14, L1-14:R6.2, L1-14:R7.1, L1-14:R8.1
M15: J2.15, L1-15:R6.2, L1-15:R7.1, L1-15:R8.1
M16: J2.16, L1-16:R6.2, L1-16:R7.1, L1-16:R8.1
M17: J2.17, J3.3, J4.1
unnamed: R10.2, U2.2
unnamed: R1.2, U2.3
unnamed: R3.1, U2.6
unnamed: R4.2, U3.2
unnamed: R7.2, U1.1
unnamed: J4.2, J4.4, R1.1, R6.1
unnamed: J3.2, J3.4, R4.1, R10.1
unnamed: PS:U1.3, U$1.1
unnamed: R6.2, U3.3
PS:N$1: PS:C1.1, PS:U1.2, PS:U2.4
PS:N$2: PS:C2.1, PS:C3.1, PS:IC1.3, PS:IC2.3, PS:U1.1
PS:N$3: PS:IC2.1, PS:R5.1, PS:R6.2
PS:N$4: PS:R1.1, PS:R2.2, PS:U2.1
PS:N$5: PS:IC1.1, PS:R3.1, PS:R4.2
PS:VOUT: PS:C4.1, PS:R1.2, PS:U2.3

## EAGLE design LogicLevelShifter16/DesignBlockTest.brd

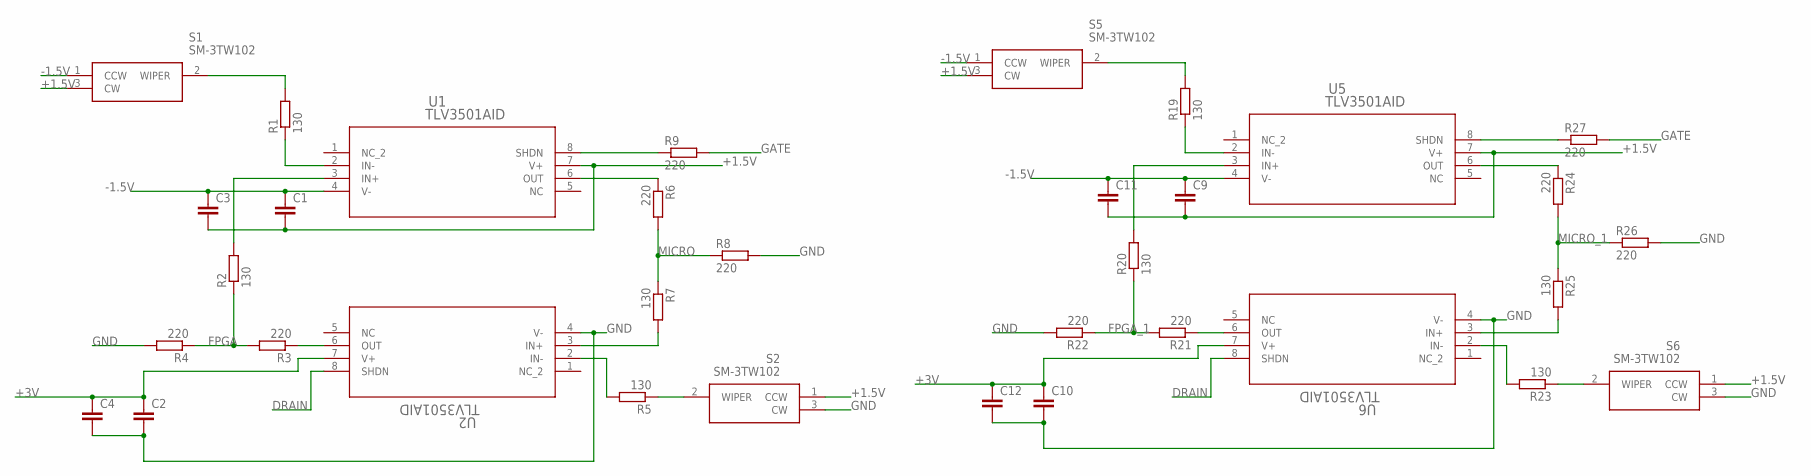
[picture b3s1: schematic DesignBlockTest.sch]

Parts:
C1, C2, C3, C4, C9, C10, C11, C12: C-EUC0805; C0805
R1, R5, R7, R19, R23, R25: 130; R0805
R2, R20: 130; R0603
R3, R4, R6, R8, R9, R21, R22, R24, R26, R27: 220; R0805
S1, S2, S5, S6: SM-3TW102; SM3TW102
U1, U2, U5, U6: TLV3501AID; D8

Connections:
+1.5V: C1.2, C3.2, C9.2, C11.2, S1.3 (CW), S2.1 (CCW), S5.3 (CW), S6.1 (CCW), U1.7 (V+), U5.7 (V+)
+3V: C2.1, C4.1, C10.1, C12.1, U2.7 (V+), U6.7 (V+)
-1.5V: C1.1, C3.1, C9.1, C11.1, S1.1 (CCW), S5.1 (CCW), U1.4 (V-), U5.4 (V-)
DRAIN: U2.8 (SHDN), U6.8 (SHDN)
FPGA: R2.1, R3.2, R4.1
FPGA_1: R20.1, R21.2, R22.1
GATE: R9.2, R27.2
GND: C2.2, C4.2, C10.2, C12.2, R4.2, R8.2, R22.2, R26.2, S2.3 (CW), S6.3 (CW), U2.4 (V-), U6.4 (V-)
MICRO: R6.2, R7.1, R8.1
MICRO_1: R24.2, R25.1, R26.1
unnamed: R1.2, S1.2 (WIPER)
unnamed: R1.1, U1.2 (IN-)
unnamed: R2.2, U1.3 (IN+)
unnamed: R3.1, U2.6 (OUT)
unnamed: R5.1, S2.2 (WIPER)
unnamed: R5.2, U2.2 (IN-)
unnamed: R7.2, U2.3 (IN+)
unnamed: R6.1, U1.6 (OUT)
unnamed: R9.1, U1.8 (SHDN)
unnamed: R19.2, S5.2 (WIPER)
unnamed: R19.1, U5.2 (IN-)
unnamed: R20.2, U5.3 (IN+)
unnamed: R21.1, U6.6 (OUT)
unnamed: R23.1, S6.2 (WIPER)
unnamed: R23.2, U6.2 (IN-)
unnamed: R25.2, U6.3 (IN+)
unnamed: R24.1, U5.6 (OUT)
unnamed: R27.1, U5.8 (SHDN)

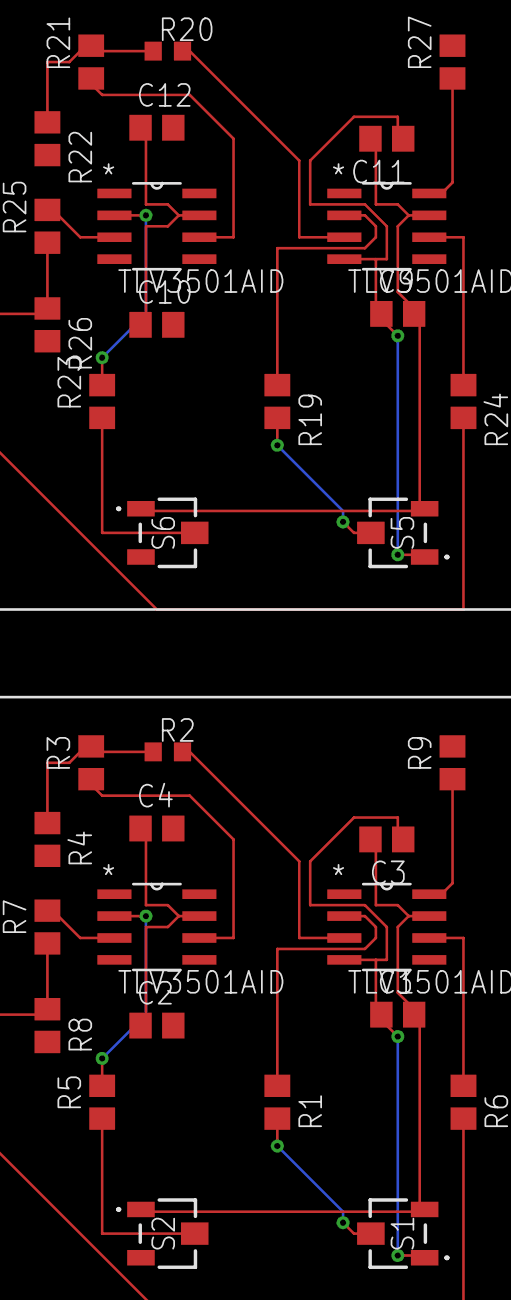
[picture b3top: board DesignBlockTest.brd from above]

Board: 2 copper layers, 34 parts (0 on the bottom side), 28 nets.
